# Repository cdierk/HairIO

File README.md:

# HairIO: Human Hair as interactive Material
Shared Repository for HairIO: Human Hair as interactive Material

# Hardware details
- Microcontroller: Arduino Nano, ordered from AliExpress. Requires [these drivers.](https://github.com/MPParsley/ch340g-ch34g-ch34x-mac-os-x-driver/)
- 

# Circuit diagram for SFCS from Disney's Touche project, as shared by Illutron
// Illutron take on Disney style capacitive touch sensor using only passives and Arduino
// Dzl 2012

```
//                              10n
// PIN 9 --[10k]-+-----10mH---+--||-- OBJECT
//               |            |
//              3.3k          |
//               |            V 1N4148 diode
//              GND           |
//                            |
//Analog 0 ---+------+--------+
//            |      |
//          100pf   1MOmhm
//            |      |
//           GND    GND
```

# Arduino code
- [mux_4052](https://github.com/cdierk/EEPP/tree/master/4052_mux_test_code) - newer version of mux that only requires two pins to select between 4 inputs. Uses [Disney's Touche that was ported to Arduino.](http://www.instructables.com/id/Touche-for-Arduino-Advanced-touch-sensing/)
- [touch_sensing_bluefruit_v2](https://github.com/cdierk/EEPP/tree/master/touch_sensing_bluefruit_v2) - Currently believe this is what's in the bluetooth-enabled demo box w/ brown hair that can actuate and communicate over bluetooth.

# Arduino pinout notes
## For mux_4052 code
- pinMode(9, OUTPUT);       //-Signal generator pin  // digital PWM
- pinMode(8, OUTPUT);       //-Sync (test) pin       // digital
- pinMode(LED, OUTPUT);
- pinMode(muxApin, OUTPUT);                          // pin 6, digital PWM
- pinMode(muxBpin, OUTPUT);                          // pin 5, digital PWM
- pinMode(braidOutput, OUTPUT);                      // pin 2, digital
- // Also uses Analog 0 later.
  
  Total: 5 digital pins, 1 analog pin.
  
## For touch_sensing_bluefruit_v2 code
// cap-sense pin
- pinMode(9, OUTPUT);       //-Signal generator pin
- pinMode(8, OUTPUT);       //-Sync (test) pin
- pinMode(drive, OUTPUT);

 //bluetooth:
- BLUEFRUIT_UART_MODE_PIN,
- BLUEFRUIT_UART_CTS_PIN, 
- BLUEFRUIT_UART_RTS_PIN

# Resources
[Instructable for Disney Touche's SFCS](http://www.instructables.com/id/Touche-for-Arduino-Advanced-touch-sensing/)

# Datasheets and Circuit Info
- [4052 mux from TI](http://www.ti.com/lit/ds/symlink/cd4051b.pdf)
- [Arduino Nano CAD files](https://forum.arduino.cc/index.php?topic=373897.0)
- [SPDT Slide switch datasheet from DigiKey](https://media.digikey.com/pdf/Data%20Sheets/C&K/SS-12D07-VG_GA_PA.pdf)
  - For Eagle, use a 1x3-pin header from Pinhead since they are also 2mm apart.

# demo
- Multiple braids w/ BLE
- Single braid w/ BLE

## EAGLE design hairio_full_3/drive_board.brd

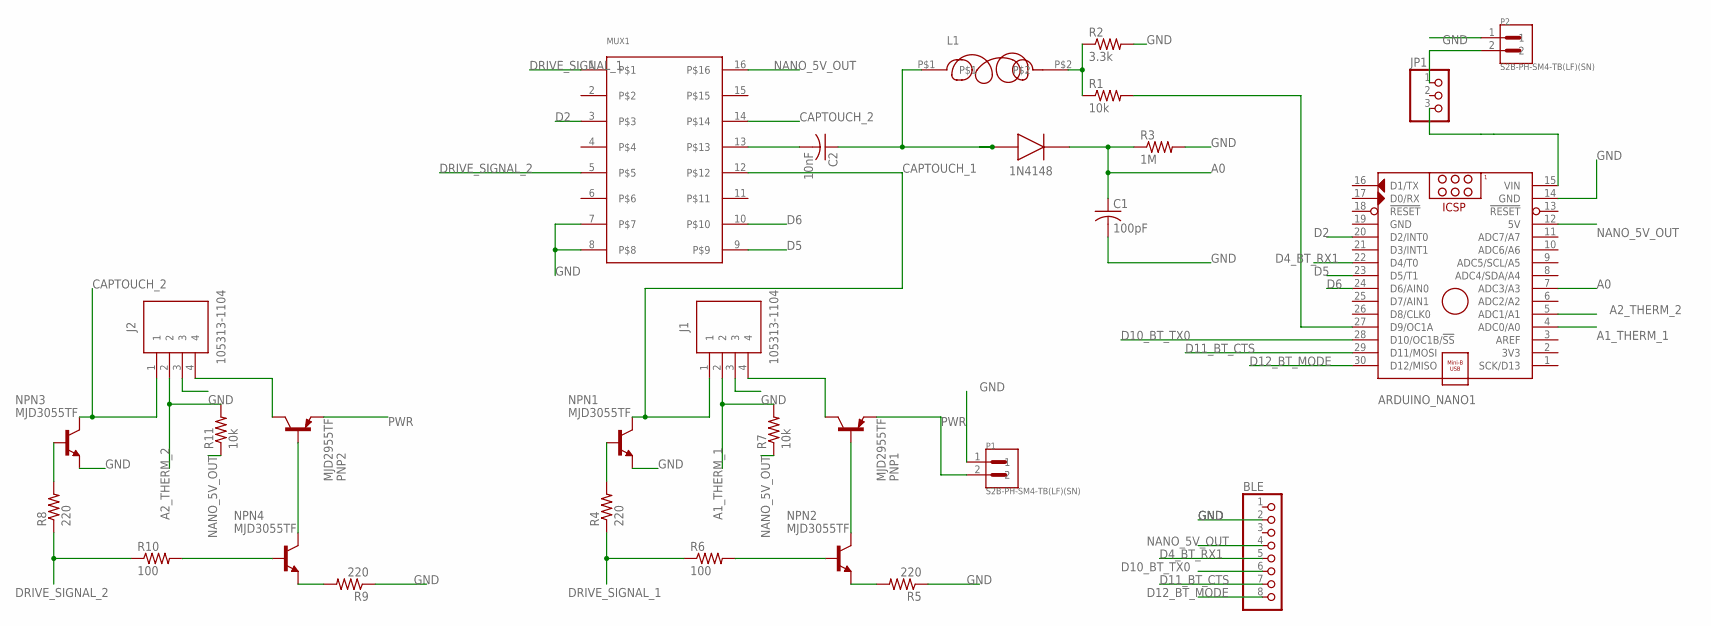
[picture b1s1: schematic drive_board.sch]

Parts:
1N4148: 1N5819HW-7-F; SOD3716X145N
ARDUINO_NANO1: ARDUINO_NANO
BLE: PINHD-1X8; 1X08
C1: 100pF; C0805
C2: 10nF; C0805
J1, J2: 105313-1104
JP1: PINHD-1X3; 1X03
L1: SRE6603
MUX1: HAIRIO_MUX; SO16
NPN1, NPN2, NPN3, NPN4: MJD3055TF; DPAK
P1, P2: S2B-PH-SM4-TB(LF)(SN); JST_S2B-PH-SM4-TB(LF)(SN)
PNP1, PNP2: MJD2955TF; DPAK
R1, R7, R11: 10k; R0805
R2: 3.3k; R0805
R3: 1M; R0805
R4, R5, R8, R9: 220; R0805
R6, R10: 100; R0805

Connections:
A0: 1N4148.1 (K), ARDUINO_NANO1.7 (ADC3/A3), C1.1, R3.1
A1_THERM_1: ARDUINO_NANO1.4 (ADC0/A0), J1.2, R7.2
A2_THERM_2: ARDUINO_NANO1.5 (ADC1/A1), J2.2, R11.2
CAPTOUCH_1: J1.1, MUX1.12, NPN1.4 (C)
CAPTOUCH_2: J2.1, MUX1.14, NPN3.4 (C)
D2: ARDUINO_NANO1.20 (D2/INT0), MUX1.3
D4_BT_RX1: ARDUINO_NANO1.22 (D4/T0), BLE.5
D5: ARDUINO_NANO1.23 (D5/T1), MUX1.9
D6: ARDUINO_NANO1.24 (D6/AIN0), MUX1.10
D10_BT_TX0: ARDUINO_NANO1.28 (D10/OC1B/!SS), BLE.6
D11_BT_CTS: ARDUINO_NANO1.29 (D11/MOSI), BLE.7
D12_BT_MODE: ARDUINO_NANO1.30 (D12/MISO), BLE.8
DRIVE_SIGNAL_1: MUX1.1, R4.1, R6.1
DRIVE_SIGNAL_2: MUX1.5, R8.1, R10.1
GND: ARDUINO_NANO1.14 (GND), ARDUINO_NANO1.19 (GND), BLE.2, C1.2, J1.3, J2.3, MUX1.7, MUX1.8, NPN1.3 (E), NPN3.3 (E), P1.1, P2.1, R2.2, R3.2, R5.1, R9.1
unnamed: NPN2.1 (B), R6.2
unnamed: NPN2.3 (E), R5.2
unnamed: NPN4.1 (B), R10.2
unnamed: NPN2.4 (C), PNP1.1 (B)
unnamed: NPN1.1 (B), R4.2
unnamed: C2.2, MUX1.13
unnamed: 1N4148.2 (A), C2.1, L1.P$1
unnamed: J1.4, PNP1.4 (C)
unnamed: ARDUINO_NANO1.27 (D9/OC1A), R1.2
unnamed: L1.P$2, R1.1, R2.1
unnamed: NPN4.3 (E), R9.2
unnamed: ARDUINO_NANO1.15 (VIN), JP1.3
unnamed: NPN4.4 (C), PNP2.1 (B)
unnamed: NPN3.1 (B), R8.2
unnamed: J2.4, PNP2.4 (C)
unnamed: JP1.1, P2.2
NANO_5V_OUT: ARDUINO_NANO1.12 (5V), BLE.4, MUX1.16, R7.1, R11.1
PWR: P1.2, PNP1.3 (E), PNP2.3 (E)

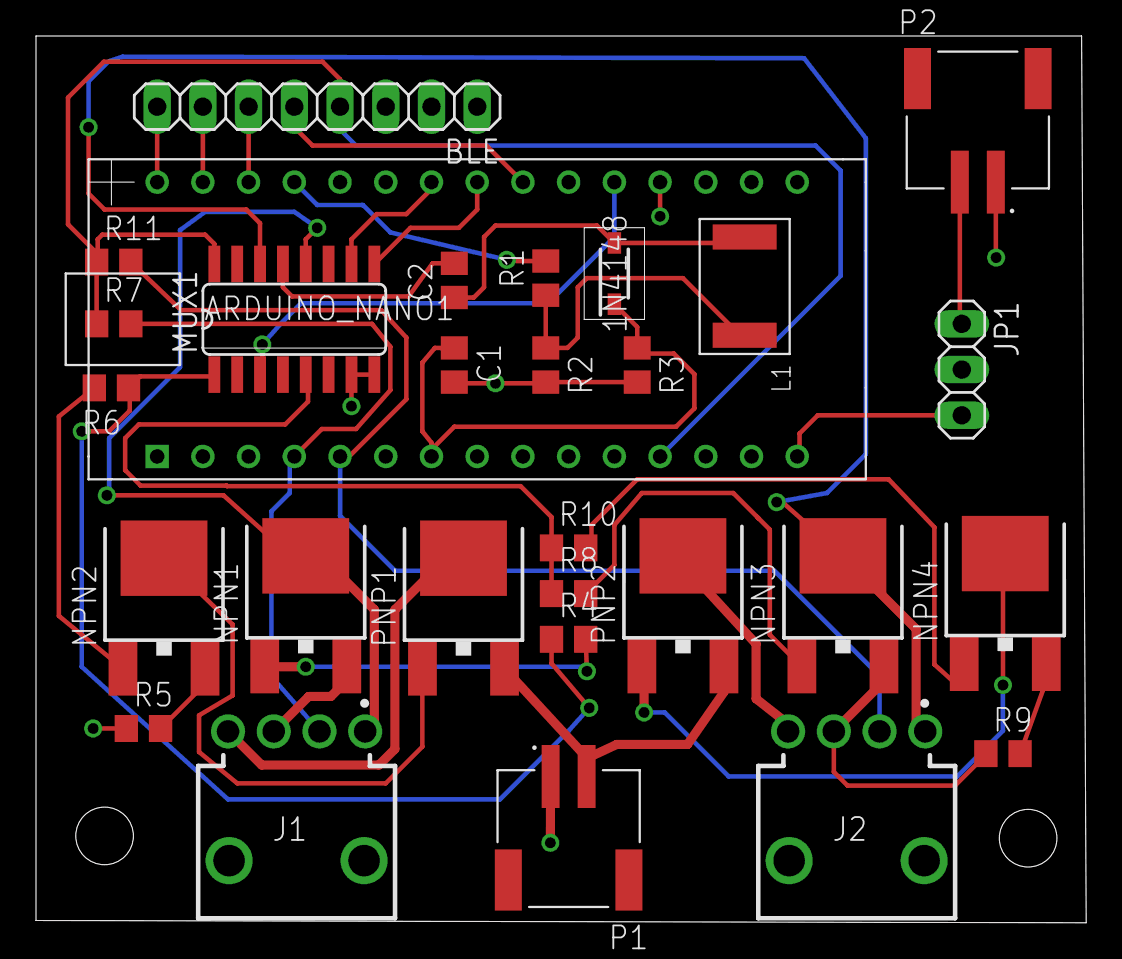
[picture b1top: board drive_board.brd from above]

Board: 2 copper layers, 58.3 x 49.3 mm, 29 parts (0 on the bottom side), 33 nets.

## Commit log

2017-07-21 arduino code for touch sensing
2017-07-21 Add first draft of hair curling, color-changing arduino code
2017-07-21 Update for circuit testing - pin 3 goes high and pin 4 goes low.
2017-07-26 Edited Arduino_sensing file to include multiplexer use
    added lines have //mux notes above them. Use with Illutron processing script to visualize. At present, cycles between two capacitive touch inputs at a rate of 5000ms (5 seconds).
2017-07-28 Basic BLE UART from hair circuit to iOS
2017-07-28 Full integrated system (input, output, bluetooth)
    Using mpr121 & bluefruit. Drive circuit is written high from Arduino pin 4.
    Does not include thermistor or multiplexor.
2017-07-29 Rearrange so it compiles on my end, go back to length 2 arrays, and remove some old code that's not being used.
2017-07-29 Use memset to set results to all zeroes instead
2017-07-29 Remove unused total_Dist variable
2017-07-29 Tidied up code and switched to LED signal instead of serial print to save bytes
2017-07-29 Updated touch_sensing file with multiplexer code
    Supports 4 braid input with one capacitive touch shield
2017-07-29 Use chars instead of ints for gesture variables to save space
2017-07-29 Remove another unused variable
2017-07-29 Debug messages.
    These confirm that the values passed into the "dist" method
    in arrays don't need to be floats - they are all of the form 158.00
    with no values ever below one. The sqrt value does end up
    having some decimal values: 172.36, but the behavior of the circuit
    seems to be just as good if we use just the int portion of those values
    (dropping the decimal values by storing it in an int instead.)
2017-07-29 Move from floats to ints in dist calculations.
2017-07-29 Remove some debug prints
2017-07-29 Move from floats to ints, after confirming no change in behavior and minimal change in values
2017-07-29 CapSensing Board + Bluefruit
    Currently writing high to pin 13 (Arduino built-in LED) rather than drive circuit. If we change this pin to a pin connected to drive circuit, everything should work!
2017-07-29 output box
2017-07-31 output box and multiplex graph
2017-07-31 Added check for capTouch disabled when driving Nitinol
2017-07-31 Edited code to stop sensing when actuating
2017-07-31 multiplexer integration with thermistor, drive, and cap; checks to limit captouch during drive; drive and thermister shut off
2017-07-31 I think this is a working version of touch sensing on one braid
2017-08-01 simple out for user study demos
2017-08-01 Circuit Diagram excluding BlueTooth
    Includes everything else: cap touch circuit, driver circuit, thermistor, arduino, batteries
2017-08-01 Circuit Diagram excluding BlueTooth
    Includes everything else: cap touch circuit, driver circuit, thermistor, batteries.
    Right now has a resistor as a stand in for the hair and says "this is the hair". Planning to doctor the image in Adobe Illustrator to include an illustrated braid. Also going to outline the different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
2017-08-01 Fixed pinouts in BluefruitConfig file
2017-08-02 Power test 1 and 2
    temperature and timing for color and shape changes (when they begin and when they finish)
    Power_test_one didn't mark anything past color end and runs for a long time (we were trying to get it to change all the way before realizing that was unfeasible).
2017-08-02 Power Test 3: 1.0A, 1.7V
2017-08-02 Power tests 4 and 5: 3.25V, 2A
2017-08-02 Power Test 6: 3.3V 2A
2017-08-04 demo code
2017-11-21 example code to test cd4052b
2018-01-23 update gitignore
2018-01-23 rename because arduino IDE didn't like the file starting with a number
2018-01-25 remove tiny lily notes
2018-02-03 demo board eagle files
2018-02-06 updated board files
2018-02-06 update comments on pins
2018-02-06 updated net class clearance
2018-02-06 polygon isolation
2018-02-08 Updated Capacitive Touch Pin to A5 (from A0)
    also added this as a global variable (capTouchPin) so that we can easily update it in the future
2018-02-08 update board
2018-02-08 hairio board with no routes between header pins
2018-02-08 change via size and shift trace
2018-02-08 More tweaks to board
2018-02-13 Before integrating multiplexer code
2018-02-13 added basic mux
    updated pin numbers in BluefruitConfig.h as well
2018-02-23 added thermistor code and braidx struct; reorganized variables. Untested.
2018-02-23 battery monitoring code, still untested
2018-02-24 working demo code with voltage monitoring for both batteries and thermistor logging
2018-03-02 new board -- the dimensioned version of what got made for demos (with ground plane fix after accidental deletion)
2018-03-03 Added debugging and REMOVED captouch (temporarily)
2018-03-08 board layout with dimensions -- modified post fabrication
2018-03-09 testing code
2018-03-12 updating demo code for two braids and captouch calibration; untested
2018-03-12 added bluetooth writes to calibration and fixed EEPROM byte reads/writes
2018-03-12 added independent braid gesture thresholds
2018-03-12 refactoring
2018-03-13 timing code and refactoring
2018-03-13 refactord braid w gesture points
2018-03-14 fixed captouch pointer problems
2018-03-14 reformat driving messages
2018-03-17 renamed demo code sketches
2018-03-18 untested captouch mini demo
2018-03-19 demo parameters for Monday -- distance captouch and 5 min delay
